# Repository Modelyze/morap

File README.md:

# MORAP: a Modular Robotic Arm Platform

### Contributors
* Viktor Kozma, KTH Royal Institute of Technology, vkozma@kth.se
* David Broman, KTH Royal Institute of Technology, dbro@kth.se

## Introduction
The MORAP system is designed to be a modular robotic arm for research purposes. It's modular in a way that modules can be designed and added or interchanged to achieve new configurations.

It is designed together with a Modelyze modeling library that allows building and simulating arm configurations, giving the user the ability to design and evaluate designs in software.

## Overall Design
The system is designed as a distributed system where each component is communicating on a standardized central data bus. This means that it's trivial to add other modules or sensors to the system.

The system has one master which controls all of the individual sub-systems and handles communication with the user. This master controller can be anything, a microcontroller, Arduino, Raspberry pi etc. The user programs this controller to fulfill specific tasks relevant to their intended application.

## Software Design
For actuation each joint have built in control electronics and tuning algorithms, providing an intuitive and easy way to control the system. The communication protocol is listed in [here](./api/) and an API implementation on a PIC32 microcontroller is listed in section [here](./api/pic32/).

Some software examples are listed [here](./applications).

## Hardware Design
The hardware is divided into joints, links and end-effectors. 

The joints provide actuation and control electronics, allowing the user to control them in multiple ways. There are also be free-running joints, like pendulums, which allows for modeling and controlling complex systems. The joints designs are found [here](./joints).

Links are the connection elements between the joints and can be anything. In this application 20x20 mm aluminum profiles are used. [possible pics?].

End-effectors are devices meant to interact with the real world. They're attached to the end of the arm and can come in different shapes, like pens or claws. Some designs can be found [here](./end-effectors).

The manufacturing process used to fabricate the necessary parts are 3d-printing.

## The Simplified BSD License

Copyright (c) 2016, Viktor Kozma and David Broman

All rights reserved.

Redistribution and use in source and binary forms, with or without
modification, are permitted provided that the following conditions are
met:

1. Redistributions of source code must retain the above copyright
notice, this list of conditions and the following disclaimer.

2. Redistributions in binary form must reproduce the above copyright
notice, this list of conditions and the following disclaimer in the
documentation and/or other materials provided with the distribution.

THIS SOFTWARE IS PROVIDED BY THE COPYRIGHT HOLDERS AND CONTRIBUTORS
"AS IS" AND ANY EXPRESS OR IMPLIED WARRANTIES, INCLUDING, BUT NOT
LIMITED TO, THE IMPLIED WARRANTIES OF MERCHANTABILITY AND FITNESS FOR
A PARTICULAR PURPOSE ARE DISCLAIMED. IN NO EVENT SHALL THE COPYRIGHT
HOLDER OR CONTRIBUTORS BE LIABLE FOR ANY DIRECT, INDIRECT, INCIDENTAL,
SPECIAL, EXEMPLARY, OR CONSEQUENTIAL DAMAGES (INCLUDING, BUT NOT
LIMITED TO, PROCUREMENT OF SUBSTITUTE GOODS OR SERVICES; LOSS OF USE,
DATA, OR PROFITS; OR BUSINESS INTERRUPTION) HOWEVER CAUSED AND ON ANY
THEORY OF LIABILITY, WHETHER IN CONTRACT, STRICT LIABILITY, OR TORT
(INCLUDING NEGLIGENCE OR OTHERWISE) ARISING IN ANY WAY OUT OF THE USE
OF THIS SOFTWARE, EVEN IF ADVISED OF THE POSSIBILITY OF SUCH DAMAGE.

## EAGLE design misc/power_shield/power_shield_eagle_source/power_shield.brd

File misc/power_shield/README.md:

# Power Shield for UNO32
A power shield designed to fit on an UNO32 designed to take input from two 4 mm lab cables, convert it to 5V and 3.3V and outputs it to two 6-pin connectors compatible with the standard connectors on the motor control chips.

Contains both Gerber and eagle source files

## Functions
* Inputs selectable voltage Vcc (>6V) through two 4 mm lab cables (Vcc and GND)
* Converts Vcc to 5V and 3.3V using two switching regulators
* Outputs Vcc, 5V, 3.3V, GND, SCL, SDA through a system standard 6 pin connector
* Contains pullup resistors for SCL and SDA line
* Contains two buttons connected to UNO32 pins 2 & 7 (RD8 & RD9)
* Contains three leds on UNO32 pins 3, 5 & 6 (RD0, RD1 & RD2) and one power LED.

## Schematic

## Bill of Material
n | value | device | package
---: | :--- | :--- | :---
1x | LM2576-5.0 | Switch Regulator 5V | TO-220-5
1x | LM2576-3.3 | Switch Regulator 3.3V | TO-220-5
2x | 1000&mu;F | Electrolytic Capacitor | 10mm Electrolytic Capacitors SMD
2x | 100&mu;F | Electrolytic Capacitor | 10mm Electrolytic Capacitors SMD
2x |  | Diode | DO-214AA=SMB
2x | 0.1mH (+1.5A) | Inductor | Radial 5mm pitch
2x | RED | LED | CHIPLED_1206
1x | GREEN | LED | CHIPLED_1206
1x | YELLOW | LED | CHIPLED_1206
1x | 1k&Omega; | Resistor | R0603
3x | 470&Omega; | Resistor | R0603
2x | 3.3k&Omega; | Resistor | R0603
2x | 10k&Omega; | Resistor | R0603
2x | | Pushbutton | Through-Hole PCB-switch
2x | 2x8 pin | Socket Header | 2.54mm pitch, long legged socket header
1x | 2x6 pin | Socket Header | 2.54mm pitch, long legged socket header
1x | 1x6 pin | Socket Header | 2.54mm pitch, long legged socket header
2x | MOLEX 3.96mm 6p | male connector | MOLEX_3.96MM_6P
1x | RED | Laboratory Socket | 15.3mm pitch PCB
1x | BLACK | Laboratory Socket | 15.3mm pitch PCB

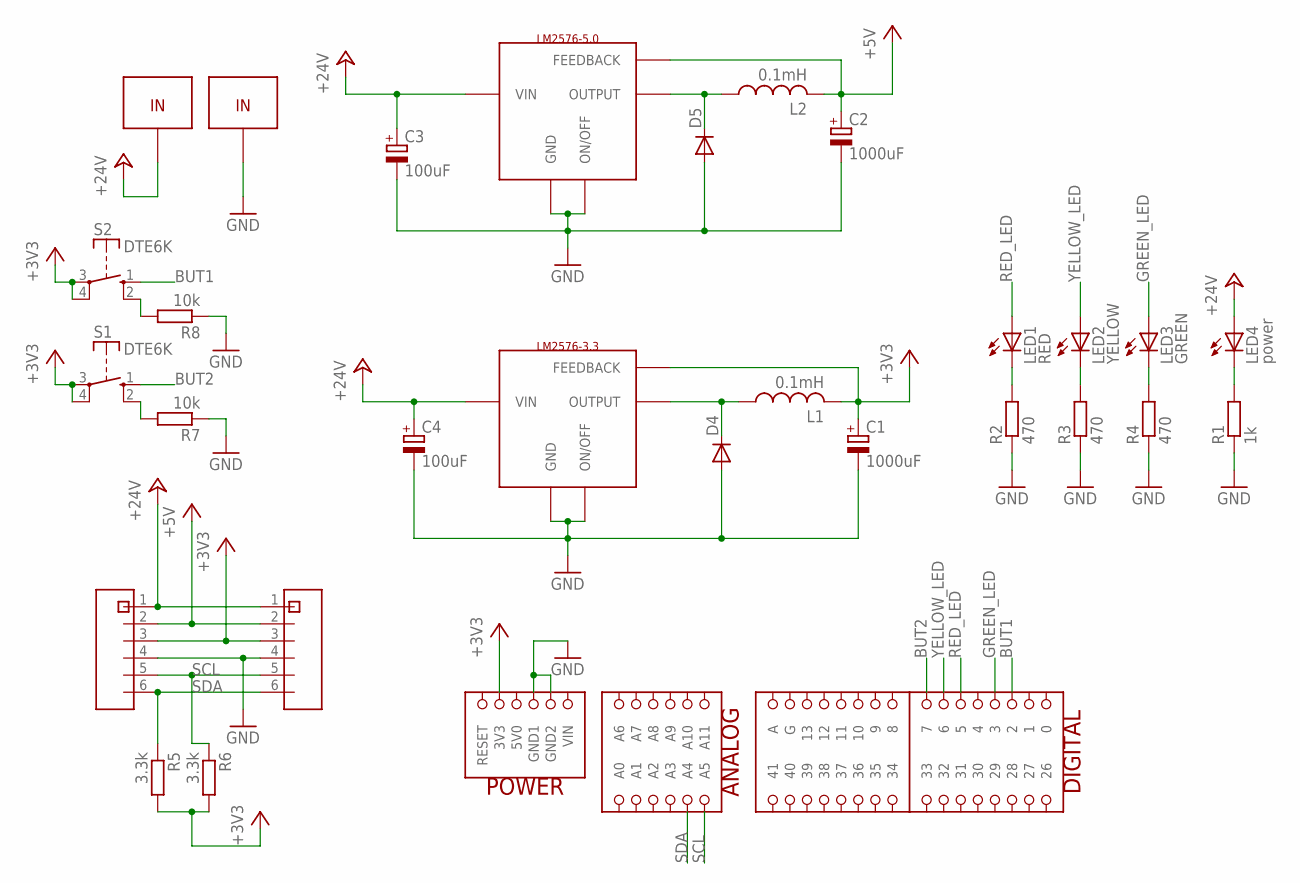
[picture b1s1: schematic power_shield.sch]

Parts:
C1, C2: 1000uF; 150CLZ-1010
C3, C4: 100uF; 150CLZ-1010
D4, D5: DIODE-DO214AA; DO214AA
L1, L2: 0.1mH; 6000-XXXX-RC
LED1: RED; CHIPLED_1206
LED2: YELLOW; CHIPLED_1206
LED3: GREEN; CHIPLED_1206
LED4: power; CHIPLED_1206
R1: 1k; R0603
R2, R3, R4: 470; R0603
R5, R6: 3.3k; R0603
R7, R8: 10k; R0603
S1, S2: DTE6K
U$1: UNO32_SHIELD
U$2: LM2576-5.0; TO-220-5
U$3: LM2576-3.3; TO-220-5
U$4, U$5: MOLEX_3.96MM_6P
U$6, U$7: LABBHYLSA

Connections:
+3V3: C1.+, L1.2, R5.2, R6.2, S1.3, S1.4, S2.3, S2.4, U$1.3V3, U$3.4 (FEEDBACK), U$4.3, U$5.3
+5V: C2.+, L2.2, U$2.4 (FEEDBACK), U$4.2, U$5.2
+24V: C3.+, C4.+, LED4.A, U$2.1 (VIN), U$3.1 (VIN), U$4.1, U$5.1, U$6.IN, U$6.IN2
BUT1: S2.1 (S), U$1.2
BUT2: S1.1 (S), U$1.7
GND: C1.-, C2.-, C3.-, C4.-, D4.A, D5.A, R1.1, R2.1, R3.1, R4.1, R7.1, R8.1, U$1.GND1, U$1.GND2, U$2.3 (GND), U$2.5 (ON/OFF), U$3.3 (GND), U$3.5 (ON/OFF), U$4.4, U$5.4, U$7.IN, U$7.IN2
GREEN_LED: LED3.A, U$1.3
unnamed: LED4.C, R1.2
unnamed: D5.C, L2.1, U$2.2 (OUTPUT)
unnamed: LED1.C, R2.2
unnamed: LED2.C, R3.2
unnamed: D4.C, L1.1, U$3.2 (OUTPUT)
unnamed: LED3.C, R4.2
unnamed: R7.2, S1.2 (S)
unnamed: R8.2, S2.2 (S)
RED_LED: LED1.A, U$1.5
SCL: R6.1, U$1.A5, U$4.5, U$5.5
SDA: R5.1, U$1.A4, U$4.6, U$5.6
YELLOW_LED: LED2.A, U$1.6

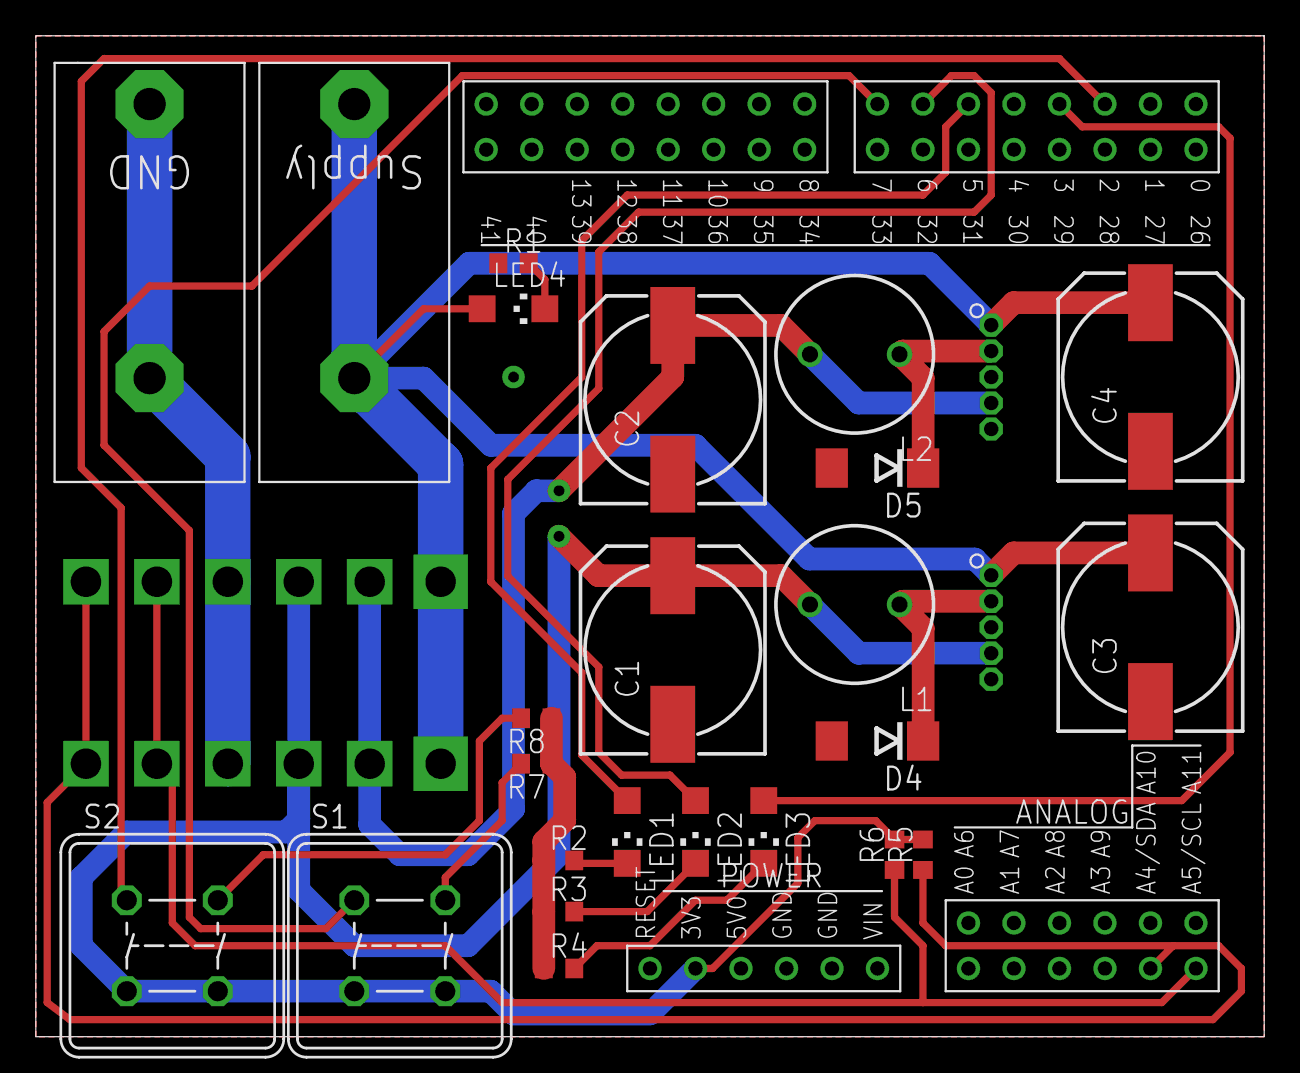
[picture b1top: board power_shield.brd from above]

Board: 2 copper layers, 68.6 x 55.9 mm, 29 parts (0 on the bottom side), 19 nets.

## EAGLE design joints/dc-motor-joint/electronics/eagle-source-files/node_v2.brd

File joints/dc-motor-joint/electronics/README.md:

# The electronics
This part contains the electronics used for 

A completed breadboard looks like:

## Schematic
The following is the schematic for the node:

## Bill of Material for Node
n | value | device | package
---: | :--- | :--- | :---
2x | 10nF | capacitor | C0603
1x | 0.1&mu;F ceramic | capacitor | C0805K
1x | 0.1&mu;F | capacitor | E5-10,5
1x | 1&mu;F | capacitor | C050-025X075
1x | 4.7&mu;F | capacitor | C0805K
2x | 22pF | capacitor | C0603
3x | 3v3 | zener diode | SOD-323 
1x | RED | LED | CHIPLED_1206
1x | GREEN | LED | CHIPLED_1206
1x | 910&Omega; | Resistor | R0603
2x | 150&Omega; | Resistor | R0603
3x | 1k&Omega; | Resistor | R0603
2x | 10k&Omega; | Resistor | R0603
1x | 560&Omega; | Resistor | R0603
1x | 32MHz | crystal | [SMD](https://www.elfa.se/en/quartz-smd-32-mhz-iqd-lfxtal052187r500/p/17451988)
1x | PIC24F32KA301 | &mu;C | SSOP-20
1x | LMD18200 | motor controller | TO-220-11
2x | MOLEX 3.96mm 6p | male connector | MOLEX_3.96MM_6P
1x | DIN41651 10P | encoder connector | DIN41651_10P
1x | 2x5.08P | screw block | 2x5.08P
1x | 6x1 pin header | pin header | 6X1P 2.54mm pin header

## Cables
The cabling between each node has a female 6 pin connector with 3.96mm raster in each end.

## Additional Electronics
An early version of an improved node board is also located here. This includes numerous improvements, such as using an LM339 voltage comparator to provide a more robust interface for reading the encoder. Another intended improvement is zoning which aims to isolate the motor driver from the rest of the circuit, which should reduce the electrical noise plaguing the current version.

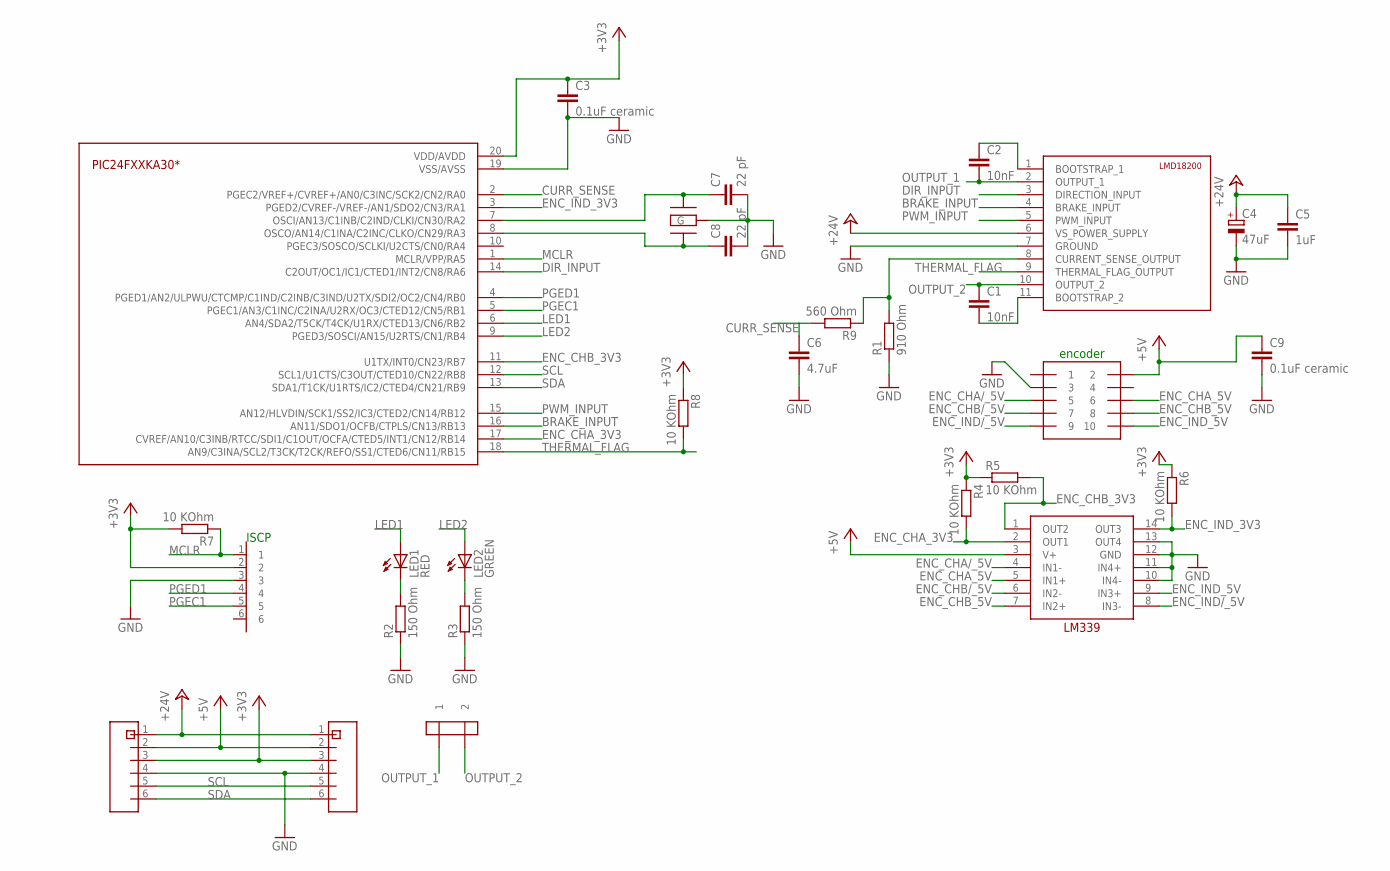
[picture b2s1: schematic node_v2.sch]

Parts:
C1, C2: 10nF; C0603
C3, C9: 0.1uF ceramic; C0805K
C4: 47uF; E5-10,5
C5: 1uF; C050-025X075
C6: 4.7uF; C0805K
C7, C8: 22 pF; C0603
LED1: RED; CHIPLED_1206
LED2: GREEN; CHIPLED_1206
R1: 910 Ohm; R0603
R2, R3: 150 Ohm; R0603
R4, R5, R6, R7, R8: 10 KOhm; R0603
R9: 560 Ohm; R0603
U$1: PIC24F32KA301; SSOP-20
U$2: LMD18200; TO-220-11
U$3, U$4: MOLEX_3.96MM_6P
U$5: DIN41651_10P
U$6: STIFTLIST_6X1P
U$7: CRYSTAL_ELFA; CRYSTAL_SMD
U$8: PCB_SKRUVPLINT_2P
U$9: LM339; SO14

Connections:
+3V3: C3.1, R4.1, R5.1, R6.1, R7.2, R8.1, U$1.20 (VDD/AVDD), U$3.3, U$4.3, U$6.2
+5V: C9.1, U$3.2, U$4.2, U$5.2, U$9.3 (V+)
+24V: C4.+, C5.1, U$2.6 (VS_POWER_SUPPLY), U$3.1, U$4.1
BRAKE_INPUT: U$1.16 (AN11/SDO1/OCFB/CTPLS/CN13/RB13), U$2.4 (BRAKE_INPUT)
CURR_SENSE: C6.1, R9.2, U$1.2 (PGEC2/VREF+/CVREF+/AN0/C3INC/SCK2/CN2/R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)
CURR_SENSE_OUTPUT: R1.2, R9.1, U$2.8 (CURRENT_SENSE_OUTPUT)
DIR_INPUT: U$1.14 (C2OUT/OC1/IC1/CTED1/INT2/CN8/RA6), U$2.3 (DIRECTION_INPUT)
ENC_CHA/_5V: U$5.5, U$9.4 (IN1-)
ENC_CHA_3V3: R4.2, U$1.17 (CVREF/AN10/C3INB/RTCC/SDI1/C1OUT/OCFA/C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), U$9.2 (OUT1)
ENC_CHA_5V: U$5.6, U$9.5 (IN1+)
ENC_CHB/_5V: U$5.7, U$9.6 (IN2-)
ENC_CHB_3V3: R5.2, U$1.11 (U1TX/INT0/CN23/RB7), U$9.1 (OUT2)
ENC_CHB_5V: U$5.8, U$9.7 (IN2+)
ENC_IND/_5V: U$5.9, U$9.8 (IN3-)
ENC_IND_3V3: R6.2, U$1.3 (PGED2/CVREF-/VREF-/AN1/SDO2/CN3/RA1), U$9.14 (OUT3)
ENC_IND_5V: U$5.10, U$9.9 (IN3+)
GND: C3.2, C4.-, C5.2, C6.2, C7.2, C8.2, C9.2, R1.1, R2.1, R3.1, U$1.19 (VSS/AVSS), U$2.7 (GROUND), U$3.4, U$4.4, U$5.3, U$6.3, U$7.2 (G), U$7.4 (G), U$9.10 (IN4-), U$9.11 (IN4+), U$9.12 (GND), U$9.13 (OUT4)
LED1: LED1.A, U$1.6 (AN4/SDA2/T5CK/T4CK/U1RX/CTED13/CN6/RB2)
LED2: LED2.A, U$1.9 (PGED3/SOSCI/AN15/U2RTS/CN1/RB4)
MCLR: R7.1, U$1.1 (MCLR/VPP/RA5), U$6.1
unnamed: C1.2, U$2.11 (BOOTSTRAP_2)
unnamed: LED1.C, R2.2
unnamed: LED2.C, R3.2
unnamed: C2.1, U$2.1 (BOOTSTRAP_1)
unnamed: C7.1, U$1.7 (OSCI/AN13/C1INB/C2IND/CLKI/CN30/RA2), U$7.3 (CRYSTAL_2)
unnamed: C8.1, U$1.8 (OSCO/AN14/C1INA/C2INC/CLKO/CN29/RA3), U$7.1 (CRYSTAL_1)
OUTPUT_1: C2.2, U$2.2 (OUTPUT_1), U$8.1
OUTPUT_2: C1.1, U$2.10 (OUTPUT_2), U$8.2
PGEC1: U$1.5 (PGEC1/AN3/C1INC/C2INA/U2RX/OC3/CTED12/C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), U$6.5
PGED1: U$1.4 (PGED1/AN2/ULPWU/CTCMP/C1IND/C2INB/C3IND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), U$6.4
PWM_INPUT: U$1.15 (AN12/HLVDIN/SCK1/SS2/IC3/CTED2/CN14/RB12), U$2.5 (PWM_INPUT)
SCL: U$1.12 (SCL1/U1CTS/C3OUT/CTED10/CN22/RB8), U$3.5, U$4.5
SDA: U$1.13 (SDA1/T1CK/U1RTS/IC2/CTED4/CN21/RB9), U$3.6, U$4.6
THERMAL_FLAG: R8.2, U$1.18 (AN9/C3INA/SCL2/T3CK/T2CK/REFO/SS1/CTED6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), U$2.9 (THERMAL_FLAG_OUTPUT)

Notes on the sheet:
encoder
ISCP

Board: 2 copper layers, 29 parts (1 on the bottom side), 34 nets, no tracks yet.

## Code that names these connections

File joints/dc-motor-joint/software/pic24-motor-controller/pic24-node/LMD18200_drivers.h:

/* 
 * File:   LMD18200_drivers.h
 * Author: vkozma
 *
 * Drivers used to control motors through the LMD18200
 * motor control chip. Includes functions and macros for
 * running the motors and reading the current.
 *
 * Designed to work with the microcontroller
 * PIC24F32KA301/302 with the following pin allocations:
 * ENABLE PIN:          RB12
 * BRAKE PIN:           RB13
 * PWM PIN:             RA6/OC1
 * THERMAL FLAG PIN:    RB15
 * CURRENT SENSE PIN:   RA0/AN0
 *
 * The PWM mode is of simple locked anti-phase type. 50 %
 * duty cycle on the PWM pin results in zero drive, 100 %
 * results in fully right and 0 % fully left. This allows
 * for an additional enable pin functionality.
 *
 * Data sheet: http://www.ti.com/lit/ds/symlink/lmd18200.pdf
 *
 * Created on May 4, 2015
 */

#ifndef LMD18200_DRIVERS_H
#define	LMD18200_DRIVERS_H

#include "main_declarations.h"
    
/*
 * Defines macros for controlling the motor
 */
#define MOTOR_ENABLE() (LATBbits.LATB12 = 1)
#define MOTOR_DISABLE() (LATBbits.LATB12 = 0)
#define MOTOR_ENABLE_SWAP() (LATBbits.LATB12 = ~(LATBbits.LATB12))
#define MOTOR_IS_ENABLED() (LATBbits.LATB12)

/*
 * If brake is on while stationary the motor will run freely,
 * if off it will be unmovable. If ON while running it won't turn,
 * if off it will turn freely.
 */
#define MOTOR_BRAKE_ON() (LATBbits.LATB13 = 1)
#define MOTOR_BRAKE_OFF() (LATBbits.LATB13 = 0)
#define MOTOR_BRAKE_IS_ON() (LATBbits.LATB13)

#define GET_THERMAL_FLAG() (PORTBbits.RB15) // If low, warning

// PWM-period in timer ticks loaded into the period register
// Needs to be uneven
#define MOTOR_PWM_PERIOD 255

// Offset the falling edge by fractions of a clock cycle using
// the DCB field, this needs to be configured if changing periods
#define DCB_OFFSET 1


// Current sensing
#define CURRENT_SENSE_RESISTOR 820.0

// The supply voltage to the motor
#define SUPPLY_VOLTAGE 24.0
// Limit voltage, is usually the same as supply voltage
#define LIMIT_VOLTAGE 20.0
// Minimum voltage, outputs below this won't get passed to the output
#define MINIMUM_VOLTAGE 0.5

// What type of PWM mode that should be used and
// whether or not the DCB bits in OC1CON2 should be
// used to increase the output resolution
#define USE_CENTER_ALIGNED_PWM
#define USE_DCB_BITS
    
/*
 * Initiates the motor pins on the board as well as the PWM timer and ADC 
 * for current sensing
 */
void init_motor(void);

/*
 * Sets the motor speed, input should be between +- the supply voltage for
 * full left and full right
 */
void set_motor_speed(float spd);

/*
 * If called with task = 0 it will perform all necessary floating point
 * calculations but not update the registers. Calling it with task = 1
 * will update the registers.
 *
 * Useful when you know you want to reduce computation time when updating
 * the motor speed when you know the speed ahead of time
 */
void set_delayed_motor_speed(float spd, unsigned char task);
#define save_motor_speed(spd) set_delayed_motor_speed(spd,0);
#define update_motor_speed() set_delayed_motor_speed(0.0,1);

/*
 * Sets the duty cycle, the input needs to be 0 <= dc <= 100
 */
void set_duty_cycle(float dc);

/*
 * Sets the OCR1 period directly, NOT implemented correctly
 */
#ifdef USE_CENTER_ALIGNED_PWM
void set_PWM_period(unsigned int rs, unsigned int r, unsigned int dcb);
#else
void set_PWM_period(unsigned int p);
#endif

/*
 * Reads the current duty cycle the motors are running at
 */
float get_duty_cycle(void);

/*
 * ADC reading functions, call ADC_sample() to start the sampling and then call
 * ADC_read to read the 12-bit sampled value.
 */
void ADC_sample(void);
unsigned int ADC_read(void);

/*
 * Read the current running through the motor
 */
float read_current(void);

/*
 * Read the voltage currently applied to the motor
 */
float read_voltage(void);

#endif	/* LMD18200_DRIVERS_H */

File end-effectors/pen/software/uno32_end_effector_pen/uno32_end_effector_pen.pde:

/*
Code for the end-effector controlled by an uno32
*/

#include <Servo.h>
#include <Wire.h>

// On-board leds
#define LED1 13
#define LED2 43

// Input
#define BUT1 2
#define BUT2 3
#define POT A0

// Servo definitions
#define SERVO_PIN 9
#define SERVO_RETRACTED 45 // 0 - 180
#define SERVO_DEPLOYED 8 // 0 - 180
#define SERVO_MEAN ((SERVO_DEPLOYED + SERVO_RETRACTED)/2)

// I2C stuff
#define I2C_ADDRESS 0b0011001
#define I2C_DEPLOY_SERVO 1
#define I2C_RETRACT_SERVO 2
#define I2C_SET_SERVO_POSITION 7

// Servo object
Servo myservo;

// variables
unsigned int sensorValue = 0, toServo = SERVO_RETRACTED;

void setup() {
  // Serial
  Serial.begin(9600);
  
  // I/O
  pinMode(LED1, OUTPUT);
  pinMode(LED2, OUTPUT);
  pinMode(BUT1,INPUT);
  pinMode(BUT2,INPUT);
  pinMode(POT,INPUT);
  
  // Servo attach
  myservo.attach(SERVO_PIN);
  myservo.write(SERVO_RETRACTED);
  
  // I2C
  Wire.begin(I2C_ADDRESS);
  Wire.onReceive(receiveEvent);
}

void loop() {
  
  //ret_to_dep(); // testing
  
  // Manual pen control through buttons  
  if(digitalRead(BUT1) == HIGH) {
    myservo.write(SERVO_DEPLOYED);
    digitalWrite(LED2,HIGH);
  } else if (digitalRead(BUT2) == HIGH) {
    myservo.write(SERVO_RETRACTED);
    digitalWrite(LED2,LOW);
  }
  delay(50);
}


void receiveEvent(int n_bytes) {  
  static unsigned char islit = 0;
  
  // Blink led for each transmission
  if (!islit) {
    digitalWrite(LED1,HIGH);
    islit = 1;
  } else {
    digitalWrite(LED1,LOW);
    islit = 0;
  }
  
  if (Wire.available() == 0) {
    return; // Safeguard
  }
  
  unsigned char command = Wire.read();
  int set_value = SERVO_RETRACTED;
  
  
  switch(command) {
    case I2C_DEPLOY_SERVO:
      set_value = SERVO_DEPLOYED;
      break;
    case I2C_RETRACT_SERVO:
      set_value = SERVO_RETRACTED;
      break;
    case I2C_SET_SERVO_POSITION:
      delay(10); // Wait for next byte to arrive
      if(Wire.available() > 0) {
        set_value = Wire.read();
        set_value = map(set_value,0,255,SERVO_RETRACTED,SERVO_DEPLOYED);
      } else {
        set_value = SERVO_RETRACTED;
      }
      break;
    default:
      set_value = SERVO_RETRACTED;
  }
  
  myservo.write(set_value);
  Serial.println(set_value);
  
  // switch on/off led depending on pen position
  if ( abs(SERVO_DEPLOYED - set_value) < abs(SERVO_RETRACTED - set_value) ) {
    digitalWrite(LED2,HIGH);
  } else {
    digitalWrite(LED2,LOW);
  }
  
  while(Wire.available() > 0); // Clear buffer
  
  delay(10); // Slight delay
}


void ret_to_dep() {
  // Test map
  unsigned char p, set_value;
  
  for(p = 0; p <= 255; p++) {
    set_value = map(p,0,255,SERVO_RETRACTED,SERVO_DEPLOYED);
    myservo.write(set_value);
    // switch on/off led depending on pen position
    if ( abs(SERVO_DEPLOYED - set_value) < abs(SERVO_RETRACTED - set_value) ) {
      digitalWrite(LED2,HIGH);
    } else {
      digitalWrite(LED2,LOW);
    }
    delay(39);
  }
  
}

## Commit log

2016-01-11 Update of readme.
2016-01-14 added email
2016-01-14 Edited some readmes and added pic32 api
2016-01-15 Added pen end effector files
2016-01-15 attempt to fix the tables
2016-01-15 attempt 2 to fix the tables
2016-01-15 Added joint software and electronics
2016-01-15 added MATLAB files
2016-01-17 Added some uno32 application of the api, they need to be tested to ensure proper functionality
2016-01-18 All uno32 applications checked and should work
2016-01-22 added application MPLAB project files
2016-01-22 Removed some files.:
2016-01-22 Updated makefile for data logger.
2016-01-22 Fixed relative path in projects
2016-01-29 Added pendulum applications
2016-02-05 Somewhat working pendulum code
2016-02-08 added hardware
2016-02-08 added bill of material to hardware
2016-02-12 Started design on a state feedback controller for pendulum
2016-02-19 Working Pendulum and some code
2016-02-23 Added assembly instructions for the dc-motor joint
2016-02-25 Some new hardware and assembly instructions
2016-03-08 Improved some joint code
2016-03-08 Added picture of the schematics of the power shield.
2016-03-08 Fixed some texts.
2016-03-08 Updated the application readme.
2016-03-08 Added pendulum readme.
2016-03-08 Added the pendulum joint
2016-03-08 updates in project and README
2016-03-08 Update readme.
2016-03-08 Fixes
2016-03-08 Some more edits.
2016-03-08 More updated.
2016-03-08 Added pendulum joint README.
2016-03-08 update pendulum
2016-03-08 Seperated the electronics
2016-03-08 Tests. Current version of the pendulum is not working.
2016-03-08 Working pendulum code, should manage to balance now
2016-03-08 Fixed some issue with nested list
2016-03-17 Added some safety check in pendulum app
2016-03-17 Minor fixes.
2016-03-17 New controller for small motor in pendulum
2016-03-17 Fixed some tuning code in pendulum
2016-03-18 Fixed and added some stuff for pendulum
2016-03-18 Added LICENSE
2016-03-18 Updated copyright.
2016-03-20 Changed to simplified BSD license.
2016-03-20 Minor update in license.
